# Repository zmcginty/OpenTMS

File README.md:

# Open-Source Transcranial Magnetic Stimulator

An open-source transcranial magnetic stimulator (TMS) project, including coil designs, pulse-generator hardware, and control/charging circuitry.

> **Safety Notice**
> This is **not** a legitimate medical device and is not a substitute for real TMS treatment. This is an experiment I built in my garage, and I cannot verify that it does what it's supposed to (if anyone wants to build an open-source MRI.... let me know...) This device is dangerous, it operates at energy levels more than enough to stop your heart, kill you, blow up and do lots of damage. If you're going to play with high energy pulsed power systems; be careful.

## Table of Contents
- [TMS Coils](#tms-coils)
- [Coil Cooling](#coil-cooling)
- [Coil Materials](#coil-materials)
- [IGBT Switches](#igbt-switches)
- [Gate Drivers](#gate-drivers)
- [Measurement System](#measurement-system)
- [Charging Circuit](#charging-circuit)
- [Pulse-Generator Designs](#pulse-generator-designs)
- [Charge-Control Circuit](#charge-control-circuit)
- [Useful Resources](#useful-resources)
- [TODO](#todo)

---

## TMS Coils

I primarily build two coil geometries — single coils and figure-8 coils. What I've focused on are air-core windings in either single-layer or multi-layer form. The general architecture is adapted from research papers and the limited information published by commercial TMS coil manufacturers. The figure-8 CloudTMS coil (below) was a major influence on my designs in terms of hollow copper conductor carrying coolant.

As I moved to higher pulse rates and energies, active cooling became necessary. My preferred approach, similar to the CloudTMS design, uses hollow copper tubing (sold for HVAC/refrigeration) insulated with PTFE heat-shrink. PTFE works well because it's a good dielectric, stays thin-walled after shrinking, tolerates high temperatures, and holds the coil shape better than thicker heat-shrink alternatives — though it does require fairly high heat to shrink fully.

**Build process:**
- Source 4mm OD / 3mm ID copper tube (5m sections) and 4.5mm, 4:1 PTFE heat-shrink in bulk.
- Feeding heat-shrink onto a long tube run takes patience — compressed air, used to create an air cushion between tube and shrink-wrap, makes this much easier.
- Wind the coil on a custom jig, either single-layer or multi-layer (multi-layer here just means winding randomly around a bobbin rather than stacking discrete single-layer coils).
- Insert something into the copper tube close to the tube's ID (weed-wacker cable works well) during the first few windings to prevent the tube from collapsing, then remove it once winding is complete.
- Hold the coil together with tape ahead of potting.

<p align="center"><em>Example coil before potting</em></p>

Potting the coil in epoxy significantly improves mechanical stability and reduces noise by keeping the windings from moving against each other under pulse forces. Hot glue works as an alternative but produces coils that are noticeably louder in operation — not confidence-inspiring at higher power levels.

<p align="center"><em>Example coil after potting</em></p>

## Coil Cooling

Coils built from hollow copper tube are cooled by pumping coolant through the winding itself.

- **Mineral oil:** Used for a long time — thinner than typical oils but thicker than water. Maintaining ~40°C required roughly 150–200 psi to push enough flow through the coil's small ID. At higher energy levels, I added a water chiller and heat exchanger to pre-cool the oil.
- **Distilled water:** More recently, I've switched to distilled water paired with a diaphragm pump, since the diaphragm provides a degree of electrical isolation between the pump mechanism and the fluid. This is simpler and more effective overall, though there is still a risk of the coolant loop reaching high voltage.

## Coil Materials

| Material | Purpose | Notes |
|---|---|---|
| [Hollow copper tube](https://www.amazon.com/dp/B082FDVNC5) | Water-cooled coil winding | Standard refrigeration-grade tube; cheap and widely available |
| [Fiberglass resin sheet](https://www.amazon.com/dp/B0DYT28W8W) | Application-side coil face | Sturdy, good electrical insulator, and appears permeable to magnetic fields — a disassembled commercial coil used what looked like FR4 fiberglass (PCB-grade) |
| [MAX EPC epoxy potting compound](https://www.amazon.com/dp/B07PMTMKZQ) | Coil potting | Inexpensive, good electrical insulator, decent thermal conductivity. For tube-cooled coils, MAX MCR (lower thermal conductivity) is also an option |

---

## IGBT Switches

My current switch of choice is the **Infineon/Eupec FZ1200R33KF2** — inexpensive and capable of handling substantial power. Prices on eBay range from ~$100–$400, and I've pushed 8kA pulses through a single unit. Adequate snubber capacitance/circuitry is essential to keep the voltage across the device under its 3.3kV rating (I target a safety margin below that).

## Gate Drivers

I've used two Power Integrations gate drivers with this IGBT:

- **2SC0535T2G0-33** — Functional, but lacks features like active clamping to protect against turn-off voltage spikes. Requires a custom PCB with gate turn-on/turn-off resistors and capacitors.
- **1SD418F2-FZ1200R33KF2** — Purpose-built for the FZ1200R33KF2; bolts directly onto the device pads. Requires only a 15VDC supply (I use a 1A source). It communicates over two fiber-optic channels (input signal and output/status), which I drive with custom PCBs using AFBR-1624Z HFBR transmitter/receiver modules, controlled by a Teensy 4.1 through a 3.3V→5V level shifter.

---

## Measurement System

### Differential Voltage Measurement
Monitoring Vce (collector-emitter voltage) across each IGBT is critical to staying within its rating — I keep a safety margin and stay below 2.5kV on 3.3kV-rated devices. Since these switches operate on the high side, measurement requires a high-voltage differential probe: I use a **Micsig DP20003** (5600V, 100MHz). A similar, lower-range HV differential probe (1300V) monitors the main capacitor bank voltage.

### Current Measurement
A shunt resistor was my first attempt but never produced a trustworthy signal. Two methods have worked well since:

1. **Rogowski coil** — Excellent for high current measurement (AC or DC, no iron core to saturate), but calibrated probes are hard to find secondhand, and a calibrated integrator circuit is needed to get a usable scope signal. I use a calibrated coil from [PowertekUK](https://powertekuk.com) — specifically the [CWTMini](https://powertekuk.com/cwtmini).
2. **Current transformer (CT)** — I use a Tektronix A621 AC current probe (rated to 2kA, available on eBay for $100–$500). In practice, it agrees with the Powertek Rogowski coil up to roughly 8kA despite the rated limit.

---

## Charging Circuit

The charging circuit is a simple, open-loop design: mains power feeds a variable transformer (variac), which drives a microwave oven transformer (MOT) to step up voltage. The stepped-up AC is rectified by a full-bridge rectifier and used to charge the main discharge capacitor bank, which is then discharged through the coil via a high-side switch (latching SCR or non-latching IGBT).

### Microwave Oven Transformers
The current two-switch flyback pulse generator uses two matched MOTs (matched by checking voltage and phase agreement between units — *measurements/resources TODO*). Drawing ~15A at 120V, two matched transformers stay below ~60°C with air cooling alone.

Earlier designs used a single MOT with low-pressure mineral-oil cooling, which worked up to ~14A — but oil cooling systems and pumps added complexity and were prone to leaks.

---

## Pulse-Generator Designs

### Design #1 — SCR-Based Pulse Generator

<p align="center"><em>SCR-switch pulse generator (SCRs are bottom-right. Main capacitor front left. Rectifier behind capacitor. and mineral-oil cooled microwave transformer behid rectifier. </em></p>

The first design I built. It handles very high energy levels well at consistent frequencies/patterns (e.g., the standard 5Hz/10Hz protocols used in early depression-treatment research). Its limitation is pattern flexibility: an SCR/thyristor is a latching switchable diode, so once triggered it fully discharges the capacitor. This steady current decay is gentle on flyback effects but rules out more complex patterns like Theta-Burst (50Hz bursts repeating at 4–5Hz).

### Design #2 — Single-IGBT Pulse Generator

<p align="center"><em>Single IGBT topology (note; two IGBTs in parallel), you can also see gate driver I used before using ones built specifically for the IGBT module</em></p>

Since IGBTs aren't latching, they can be switched on and back off within a short pulse, allowing partial capacitor discharge and enabling patterns like Theta-Burst. The tradeoff is significant flyback voltage when interrupting current through the coil — this destroyed several IGBTs before I addressed it with a robust flyback diode across the coil and snubber capacitors across the IGBT(s) to absorb spikes from parasitic wiring/busbar inductance. HV differential probes are essential here to stay within the switch's voltage rating while tuning.

This design uses a flyback diode across the coil, producing a sharp current rise but a slow fall (as flyback energy dissipates through coil/wire resistance and the diode). It worked well and was relatively simple compared to the two-switch flyback design, but since flyback energy isn't recycled, it's ultimately limited by the 120V/15A charging circuit.

### Design #3 — Two-Switch Flyback IGBT Pulse Generator

<p align="center"><em>Two-Switch flyback topology being built. You can see the diodes hanging off to the sides. And gate drives are now on the left, bolted to IGBT modules behind bus-bars.</em></p>

This design recycles more pulse energy than the single-IGBT version and produces both a sharp rising *and* falling current edge, increasing di/dt for a stronger but shorter magnetic field pulse. It noticeably reduced charging-circuit current draw and appears more effective at stimulating muscle/nerve tissue than the single-switch design, even at higher peak current — likely because faster field transitions induce greater current in tissue.
+ For this design it's important to thermally bond both IGBT/switch modules so that they're the same temperature and have the same switching characteristics. For this I bolt them each to opposite sides of an aluminum plate which I attach water-cooling blocks to.
I've been realizing the importance of keeping switching loops tight, and have shortened cabling from capacitor to IGBTs, and shortening cables from IGBTs to diodes.

<p align="center"><em>Photo of the system, from left-to-right; charge-control board, multimeter, main pulse-IGBTs (with many red snubber caps), charge-control IGBT (with single red snubber in front), charge-circuit-rectifier, and main pulse capacitor bank in back </em></p>

### Design #4 — H-Bridge IGBT Pulse Generator (Not Yet Built)
Should double coil pulse current relative to the two-switch flyback topology by enabling current reversal. The complexity of positioning four large IGBT switches and the associated snubbers and diodes close to eachother, with cooling is going to be difficult without adding parasitic inductance that would offset the gains.

---

## Charge-Control Circuit

<p align="center"><em>Newly Built Charge-Control Board with (from bottom to top) Teensy 4.0, ADS8699 high-speed ADC, AD5693 DAC, LM393P Comparator, ADS1115 4ch slow ADC, 5V LDO, and 3.3V buck-converter</em></p>

The new charge-control system seems to be working well enough for calling it version 1!!! After many failed attempts to measure a voltage divider, and my ground plane shifting and making either the teensy and/or ADC shit itself, even after adding digital SPI isolators, I realized.... that's what HV diff probes are for! So ripped out some HV SPI/I2C isolators and I'm now just measuring the output of a Micsig 1300v diff probe. No glithes, no isolators causing signal delays, no fried chips and salsa. Perfect.

The new approach uses a DAC to output a reference voltage into a comparator, which compares it against the output of the Micsig 1300v differential probe. I have probe scale-factors in the teensy code as well as linear calibrations for both ADCs and DAC as well. I have the fast ADC on here as well incase I want to control the charge-circuit via the teensy reading ADC instead of from the comparator + DAC, but for now the comparator + DAC method is working great, so we have some extra/redundant ADCs. A weak pull-down on the DAC output ensures that if the microcontroller glitches or crashes, the DAC voltage falls to zero and the charge circuit fails safely.

<p align="center"><em>Screenshot of a python script which displays a realtime graph and telemetry from the serial output of the teensy charge-control. Also added the ability to adjust the charge-setpoint in the python window. You can see the pulse trains as the capacitor discharges, and the charge controller working as it limits the capacitor voltage at the setpoint of (close to) 100V!</em></p>

Above is a screenshot of a python script which listens to voltage values sent over serial from the teensy charge controller and will display a live graph of the capacitor voltage, which is really useful for debugging as it's basically an autoscaling slow oscilliscope. The graph only shows the fast ADC's (ADS8699) calibrated capacitor voltage. It also displays other, slow-speed telemetry as numbers such as the slow ADC's calibrated capacitor voltage, slow ADC's measurement of DAC's output in both raw voltage, and the scaled/calibrated set-voltage it corresponds to (ie. I set the DAC to output a voltage which corresponds to 200V from the Micsig, I can verify that the ADC's measurement reads close enough, like 199.2V) I also added control to adjust the voltage setpoint from this python window which is useful for testing system starting from low voltage to be safe. I think there may be something with the comparator which is causing the cutoff to be slightly below the setpoint; in the screenshot you can see it cutting at ~95V instead of 100V. More calibrations....

## Upgrades to Pulse-Driver system

<p align="center"><em>Pulse Driver Board with added inputs for RX signals from fiber-optic interface board, level-shifter and fault LED</em></p>

I've made some additions to the pulse-driver control circuit as well; for a while I was just sending pulses from the teensy to the fiber-optic transmitters to fire the IGBT switches, and not reading the signal received from the other fiber line which acknowledges the driver received each pulse, and can indicate faults like a short-circuit. I wired up the fiber RX lines, ran them through a level shifter to 3.3v for the teensy to read and the teensy is now checking that each pulse was ack'd by each gate-driver, and can turn on the big-red fault LED if something's wrong. NOTE: Big-Red Fault LED will blink if the teensy detects a warning; like a an ack pulse was slightly off, or short/long. The LED will latch on if it detects a fault such as a short-circuit. It also prints this data + occasional status out over serial. The teensy code has the ability to control a safety relay to shut off main power to the system if a fault is detected, but I don't have that safety mechanical relay wired in yet, so for now, it just keeps going.

---
## Coil Field Simulation
While I've built coils similar to what other systems use, I have difficulty understanding how fields from multiple coils interract/interfere to create focused peaks. I've asked Claude to build some tools to help visualise magnetic field strength in a 3-d map of various types of coils here [Coil_Field_Simulator_Scripts](Coil_Field_Simulator_Scripts/).
 The simulations show for instance what happens to the field when you reverse current of one of the two figure-8 windings, or have the two coils overlap. I'm hoping that I can gather data with the Coil-Field Measurement System mentioned below, to confirm what these simulations show.
I know that TMS companies construct special coils for studies called "sham-coils" which are meant to make the same sound, but the windings are wired such that the two halves of the figure-8 cancel out. These coils are used for TMS efficacy studies to give someone placebo treatment. 

## Coil Field Mapping System
I've begun the coil-measurement system! at the moment I only have the data-acquisition side built and working which is in [Coil-Field_Measurement_DAQ](Coil-Field_Measurement_DAQ/), and will have to integrate this with a 3-axis machine to move a probe around the coil to take measurements. 
As much as I wanted to use a high-speed ADC and teensy to measure pulses, it would have been alot of work to read and buffer 1M samples/s.... So I decided to use a faster USB oscilliscope instead; [DreamSourceLab DSCope](https://www.dreamsourcelab.com/product/dscope-series/) and had Claude write some python scripts which access it via the sigrok library, and visualize the results of the measurements it takes. Note; the scope I have which this code is built to interface with is a DSCope B20. 
- CH0 of the scope is measuring custom magnetic probe (a small coil of magnet-wire connected to RG316 shielded cable) 
- CH1 of the scope measures a rogowski current probe measuring the current through the coil, this is so the magentic fieldn strength can be scaled by the measured current to account for any difference in pulse strength.

## Safety Resources
- [TMS Safety with respect to seizures](https://pmc.ncbi.nlm.nih.gov/articles/PMC7732158/pdf/ndt-16-2989.pdf)
- [General article discussion factors which can decrease seizure-threshold (make it more likely you'll have a seizure)](https://www.wmchealth.org/living-well/7-everyday-factors-that-can-increase-seizure-risk)
- [Concise overview from clinic of seizure risk factors](https://www.midcitytms.com/transcranial-magnetic-stimulation-safety-with-respect-to-seizure-ndt/)

## Useful Resources

- [Online calculator used for Beam-Protocol/10-20 system to calculate position of DLPFC](https://clinicalresearcher.org/F3/calculate.php)
- [Same online calculator, where you enter your measurements](https://clinicalresearcher.org/F3/)
- [Clinical Researcher Software Tools (where I got the two links above) Contains other tools that could be useful for motor-threshold stuff](https://clinicalresearcher.org/software.htm)

## Useful Videos
- [Coil placement and the 10-20 system/beam protocol (video)](https://youtu.be/CKCvAkgdJuY?si=6TRw3_EgRK5eAh5G)
- [Same video as above with added instructions to enter measurements into clinicalresearcher calculator (link above)](https://youtu.be/akp4V5PFb6A?si=kvKB5cpgHWPCvdm8)
- [Good introductory explanation of general TMS](https://www.youtube.com/watch?v=NQHVfF_5rtc)
- [Funny video of the TMS researcher interrupting his speach with TMS](https://www.youtube.com/watch?v=85QKdt8boMA)
- [Researcher showing TMS stimulating muscles directly and muscles through the motor-cortex](https://www.youtube.com/watch?v=JA0q4fVqrFQ)
- [Good Long-Form explanation of someone who runs a TMS clinic showing how they get a patient setup, and perform treatment](https://www.youtube.com/watch?v=WxCunEG2oi0)

## TODO
1. **UPDATE THE SCHEMATICS**
2. **Refine charge-control switch** The charge controller is working well now. But I'm using a rediculously big IGBT to switch just a few tens of amps. Need to find a smaller IGBT/switch which can withstand ~2-3kV to be on the safe-side.
3. **Build a phase-control rectifier** This is to replace the HV charge circuit's current rectifier and eliminate the variac, integrating it into the charge system. I think I'll need some kind of PID control of phase/firing angle. This could also replace the current bang-bang charge-control system for controlling main capacitor-bank charge-level.
4. **Process gate-driver fault feedback** Reading status/feedback from gate-drivers is working now and has latching/blinking LEDs/indicators to indicate warnings and faults. There is functionality to turn off a safety relay, disconnecting power from a subsystem or whole system which I'll get wired up later.
5. **Extend functionality to Pulse-Driver Teensy** I'd like to add the ability to run different patterns/protocols, maybe add input (with damn good shielding) so user can press a button to fire a single pulse. And add the ability to choose different pulse-patters, like various continuous or intermittent rTMS(repetitive) frequencies. Also various TBS-based protocols (Thea-Burst Stim); continuous (cTBS) and intermittent (iTBS) with adjustments for various parameters such as train-frequency, inter-train delay and such.
6. **Finally build a tool to map the magnetic field strength & shape of a coil.** My idea is basically put a precise analog hall-effect sensor on some 3d gantry machine like a 3d printer, and have it scan over many 3d points around the coil and create a 3d heat-map of magnetic field strength. Anyone know how to use 3d-printers? and know how to make them scan some end-effector to create a map like this???? I'd love some help!
7. **Better Shielding / Shielded Enclosure** This is basically a small EMP... so I find myself having to filter out interference on EVERYTHING at exactly the time the IGBT turns off (the turn-off spike). What if I just put everything in a shielded/grounded metal box??? Surely it wouldn't be that easy right??
8. **Create Bill-Of-Materials for each design** Create BOMs for what parts I've used in the various designs of TMS systems. Most coil materials are the same. But it would be useful to have BOMs for the SCR-based and IGBT-based pulse-generator designs.
9. **Maybe implement Micsig's command and control protocol over USB/serial** Micsig's command and control interface can configure the voltage range and bandwidth of the probe, and can read the probes serial number. Reading the serial number would allow the control software to load a specific calibration for a specific serial number of probe to ensure accuracy. Could also have a fallback/safe mode the system could operate in when connected to uncalibrated probes.

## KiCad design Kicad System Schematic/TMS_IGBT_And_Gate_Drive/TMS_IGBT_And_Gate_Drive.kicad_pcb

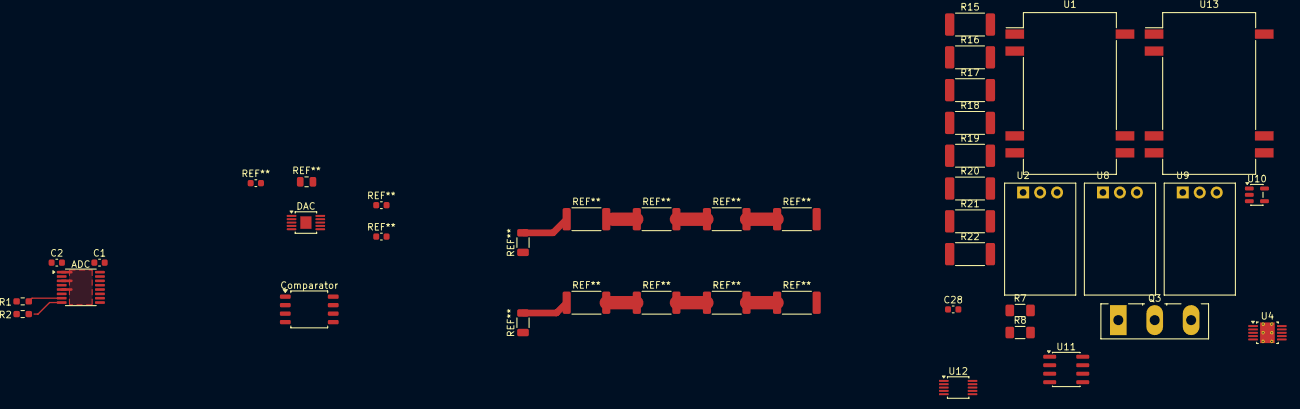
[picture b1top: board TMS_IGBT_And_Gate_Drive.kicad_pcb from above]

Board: 2 copper layers, 28 parts (0 on the bottom side), 15 nets.

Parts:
ADC: ADS8699IPWR; TSSOP-16_4.4x5mm_P0.65mm
C1, C2: C_0603; C_0603_1608Metric
C28: 10000p; C_0603_1608Metric
Comparator: LM293DR; SOIC-8_5.3x5.3mm_P1.27mm
DAC: AD5683RARMZ; MSOP-10-1EP_3x3mm_P0.5mm_EP1.68x1.88mm
Q3: IRG4PF50W; TO-247-3_Vertical
R1, R2: R_0603_1608Metric_Pad0.98x0.95mm_HandSolder
R7, R8: 10K; R_1206_3216Metric_Pad1.30x1.75mm_HandSolder
R15, R16, R17, R18, R19, R20, R21, R22: 1M; R_2512_6332Metric_Pad1.40x3.35mm_HandSolder
U1, U13: Isolated DC-DC Converter; Converter_DCDC_Artesyn_ATA_SMD
U2, U8, U9: Non-Isolated DC-DC Converter; Converter_DCDC_Murata_OKI-78SR_Horizontal
U4: AD5693RxRM; AD5683RARMZ
U10: MCP1415; SOT-23-5
U11: LM2931-5.0_SO8; SOIC-8_3.9x4.9mm_P1.27mm
U12: ADS1115IDGS; TSSOP-10_3x3mm_P0.5mm

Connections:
+5V: U2.3 (OUT), U8.1 (IN)
+8V: U9.3 (OUT), U11.8 (IN)
+24V: U1.16 (+VIN), U2.1 (IN), U9.1 (IN), U13.16 (+VIN)
GND: C28.2, Q3.2 (C), R7.1, R8.1, U1.1 (-VIN), U2.2 (GND), U8.2 (GND), U9.2 (GND), U11.2 (GND), U11.3 (GND), U11.6 (GND), U11.7 (GND), U12.3 (GND), U12.5 (AIN1), U12.6 (AIN2), U12.7 (AIN3), U12.8 (VDD), U13.1 (-VIN)
ISO_+15V: U1.9 (+VOUT), U10.2 (Vdd), U13.9 (+VOUT)
ISO_GND: U1.10 (-VOUT), U10.4 (GND), U13.10 (-VOUT)
unnamed: R15.2, R22.2
unnamed: R15.1, R16.2
unnamed: R16.1, R17.2
unnamed: R17.1, R18.2
unnamed: R19.2, R20.1
unnamed: R20.2, R21.1
unnamed: R21.2, R22.1
unnamed: R7.2, R19.1
unnamed: R8.2, R18.1, U12.4 (AIN0)

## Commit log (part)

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2024-11-07 added readme with simple zero-fucks description... it's a start.
2024-11-07 slightly better description of pulse-generator types.
2024-11-08 adding gitignore to ignore annoying macos files
2024-11-08 added a few basic photos of both IGBT-type and SCR-type pulse-generators, and a few photos of one oil-cooled TMS-coil
2024-11-09 adding janky schematic/layout or whatever it is for the IGBT pulse generator
2024-12-03 updated readme with basic-bitch legal CYA, and updated IGBT-based pulse-gen description.
2024-12-03 formatting
2024-12-03 added Arduino sketch which I'm using in the SCR-based TMS pulse-generator
2024-12-03 added super simple pulse generator I'm using to test IGBT-based TMS pulse-generator, this sketch has adjustments to send pulse trains
2024-12-19 wrote up some more documentation for coils (which I've been trying some new designs lately), and some general notes on charging system, and cooling systems I've found I needed to run this system at d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
2024-12-19 added photos of newest coil assembly pre and post epoxy potting, a few pictures of giant capacitors, probs a picture of my janky workbench containing TMS V3 in all it's glory. Someday..... I promise 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
2025-11-28 reorganized existing stuff into Designs #1,#2,#3, and #4 and added design #3; two-switch flyback IGBT pulse generator
